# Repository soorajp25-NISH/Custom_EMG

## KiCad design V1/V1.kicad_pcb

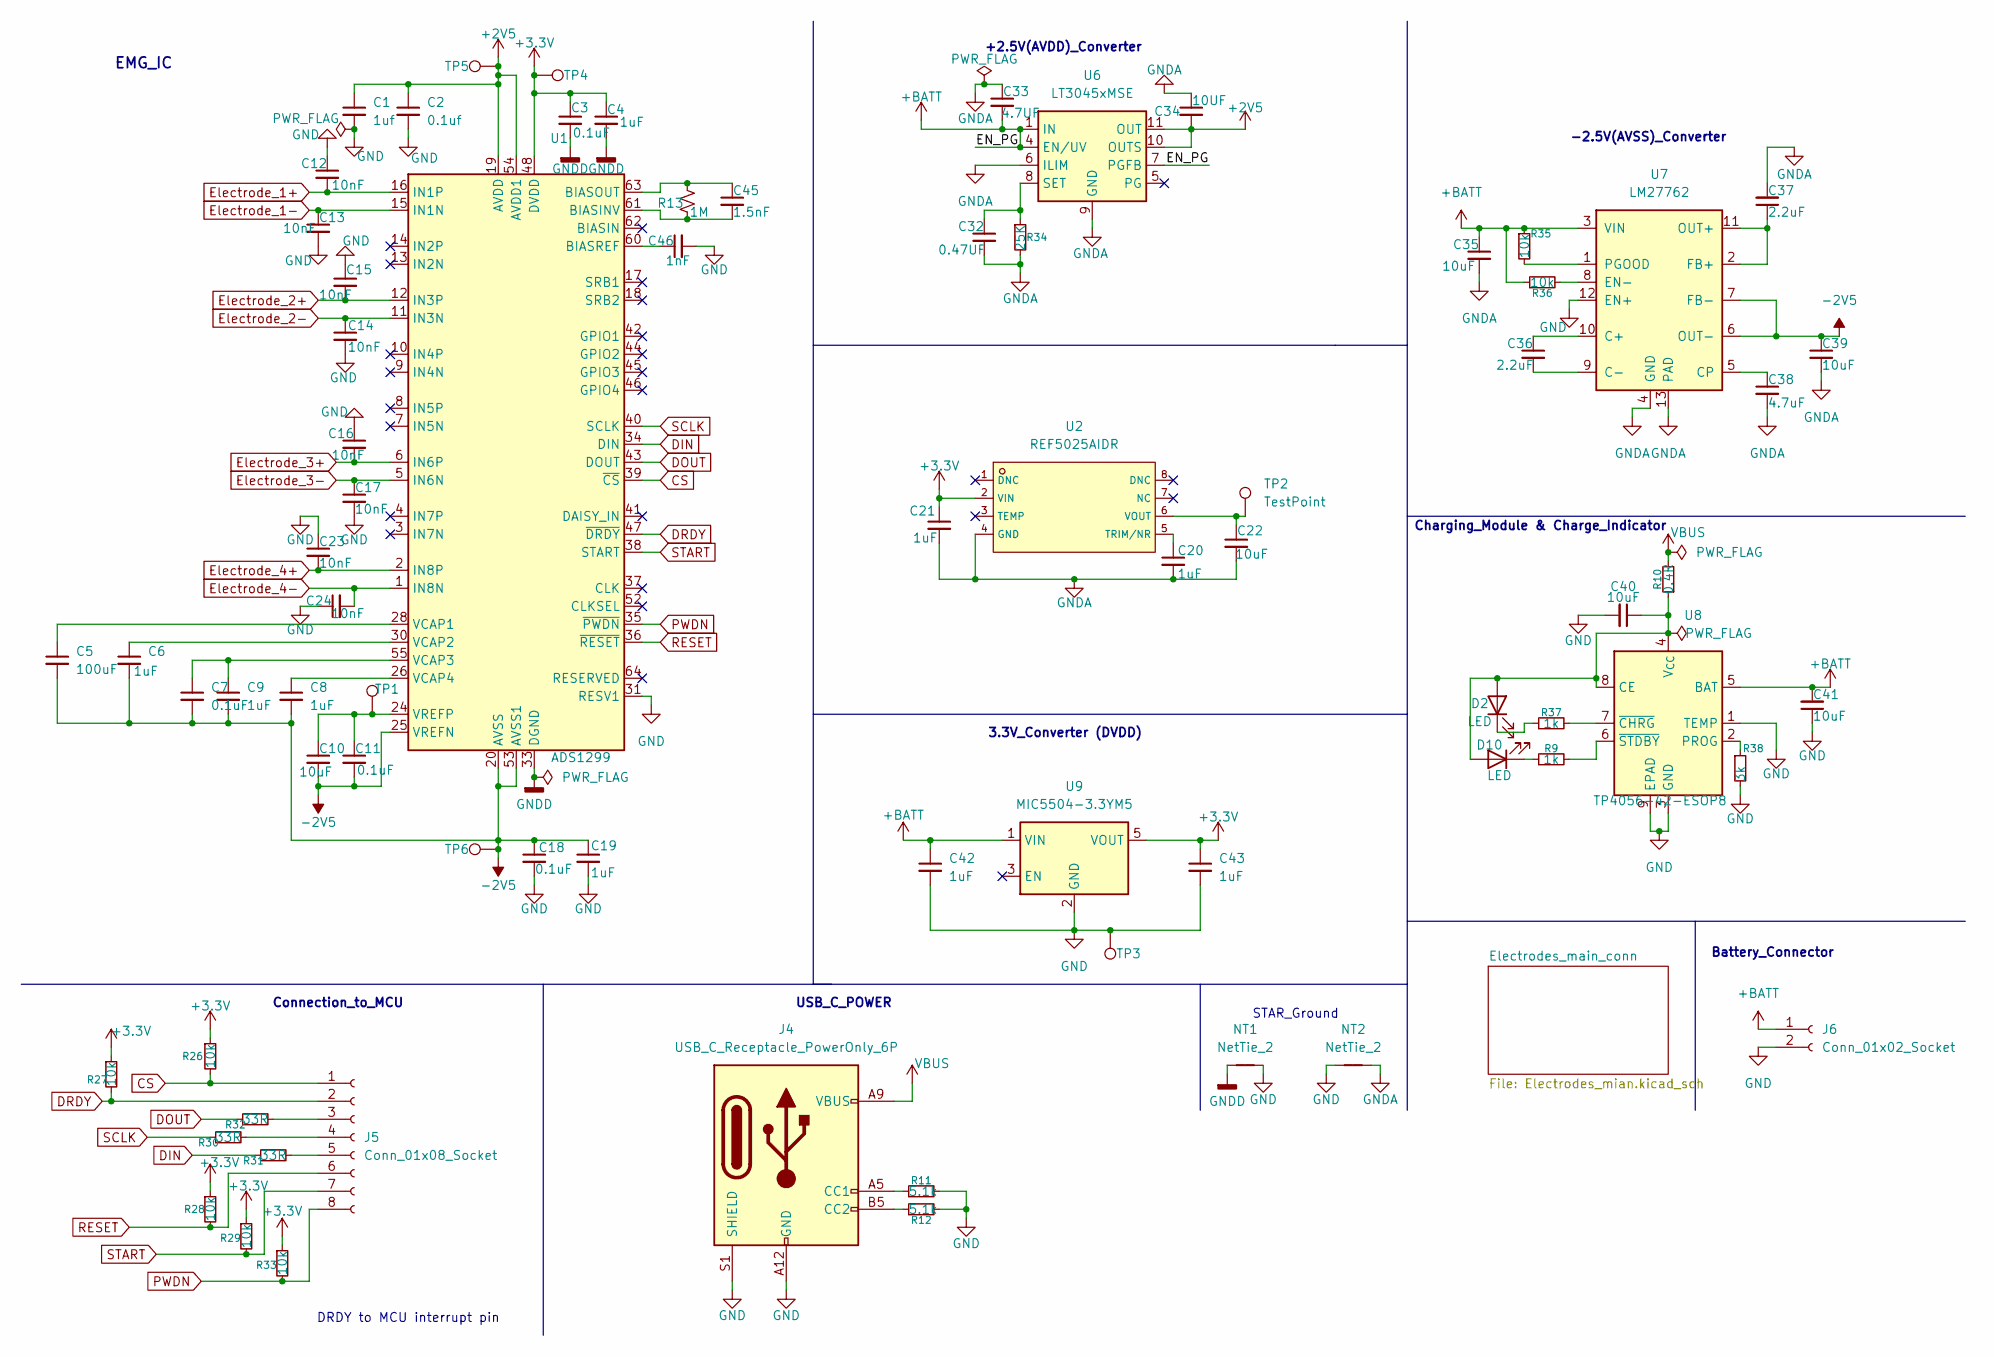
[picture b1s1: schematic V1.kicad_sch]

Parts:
C1: 1uf; C_0402_1005Metric
C2: 0.1uf; C_0402_1005Metric
C3, C7, C11, C18: 0.1uF; C_0402_1005Metric
C4, C6, C8, C9, C19: 1uF; C_0402_1005Metric
C5: 100uF; C_0603_1608Metric
C10, C35, C40, C41: 10uF; C_0603_1608Metric
C12, C13, C14, C15, C16, C17, C23, C24: 10nF; C_0402_1005Metric
C20, C21: 1uF; C_0603_1608Metric_Pad1.08x0.95mm_HandSolder
C22, C39: 10uF; C_0603_1608Metric_Pad1.08x0.95mm_HandSolder
C32: 0.47UF; C_0402_1005Metric
C33: 4.7UF; C_0603_1608Metric
C34: 10UF; C_0603_1608Metric
C36, C37: 2.2uF; C_0603_1608Metric
C38: 4.7uF; C_0603_1608Metric
C42, C43: 1uF; C_0603_1608Metric
C45: 1.5nF; C_0402_1005Metric
C46: 1nF; C_0402_1005Metric
D2, D10: LED; LED_0603_1608Metric_Pad1.05x0.95mm_HandSolder
J4: USB_C_Receptacle_PowerOnly_6P; USB_C_Receptacle_GCT_USB4135-GF-A_6P_TopMnt_Horizontal
J5: Conn_01x08_Socket; PinHeader_1x08_P2.54mm_Vertical_SMD_Pin1Right
J6: Conn_01x02_Socket; PinHeader_1x02_P2.54mm_Vertical
NT1, NT2: NetTie_2; NetTie-2_SMD_Pad0.5mm
R9, R37: 1k; R_0603_1608Metric_Pad0.98x0.95mm_HandSolder
R10: 0.4R; R_0603_1608Metric_Pad0.98x0.95mm_HandSolder
R11, R12: 5.1k; R_0603_1608Metric_Pad0.98x0.95mm_HandSolder
R13: 1M; R_0805_2012Metric
R26, R27, R28, R29, R33, R35, R36: 10k; R_0603_1608Metric_Pad0.98x0.95mm_HandSolder
R30, R31, R32: 33R; R_0603_1608Metric_Pad0.98x0.95mm_HandSolder
R34: 25K; R_0201_0603Metric_Pad0.64x0.40mm_HandSolder
R38: 3k; R_0603_1608Metric_Pad0.98x0.95mm_HandSolder
TP1, TP2, TP3, TP4, TP5, TP6: TestPoint; TestPoint_Pad_1.0x1.0mm
U1: ADS1299; TQFP-64_10x10mm_P0.5mm
U2: REF5025AIDR; SOIC-8_L4.9-W3.9-P1.27-LS6.0-BL; LCSC C11341
U6: LT3045xMSE; MSOP-12-1EP_3x4.039mm_P0.65mm_EP1.651x2.845mm
U7: LM27762; WSON-12-1EP_3x2mm_P0.5mm_EP1x2.65_ThermalVias
U8: TP4056-42-ESOP8; SOIC-8-1EP_3.9x4.9mm_P1.27mm_EP2.41x3.3mm_ThermalVias
U9: MIC5504-3.3YM5; SOT-23-5

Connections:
+2V5: C1.1, C2.1, C34.2, TP5.1, U1.19 (AVDD), U1.21 (AVDD), U1.22 (AVDD), U1.54 (AVDD1), U1.56 (AVDD), U1.59 (AVDD), U6.10 (OUTS), U6.11 (OUT), U6.12 (OUT)
+3.3V: C3.1, C4.1, C21.1, C43.1, R26.1, R27.1, R28.1, R29.1, R33.1, TP4.1, U1.48 (DVDD), U1.50 (DVDD), U2.2 (VIN), U9.5 (VOUT)
+BATT: C33.2, C35.1, C41.2, C42.1, J6.1, R35.1, R36.1, U6.1 (IN), U6.2 (IN), U6.3 (IN), U6.4 (EN/UV), U6.7 (PGFB), U7.3 (VIN), U8.5 (BAT), U9.1 (VIN)
-2V5: C5.2, C6.2, C7.2, C8.2, C9.2, C10.2, C11.2, C18.1, C19.1, C39.1, TP6.1, U1.20 (AVSS), U1.23 (AVSS), U1.25 (VREFN), U1.32 (AVSS), U1.53 (AVSS1), U1.57 (AVSS), U1.58 (AVSS), U7.6 (OUT-), U7.7 (FB-)
CS: J5.1, R26.2, U1.39 (~CS)
DIN: R31.1, U1.34 (DIN)
DOUT: R32.1, U1.43 (DOUT)
DRDY: J5.2, R27.2, U1.47 (~DRDY)
Electrode_1+: C12.2, U1.16 (IN1P); also elsewhere on the board
Electrode_1-: C13.1, U1.15 (IN1N); also elsewhere on the board
Electrode_2+: C15.2, U1.12 (IN3P); also elsewhere on the board
Electrode_2-: C14.1, U1.11 (IN3N); also elsewhere on the board
Electrode_3+: C16.2, U1.6 (IN6P); also elsewhere on the board
Electrode_3-: C17.1, U1.5 (IN6N); also elsewhere on the board
Electrode_4+: C23.2, U1.2 (IN8P); also elsewhere on the board
Electrode_4-: C24.2, U1.1 (IN8N); also elsewhere on the board
GND: C1.2, C2.2, C12.1, C13.2, C14.2, C15.1, C16.1, C17.2, C18.2, C19.2, C23.1, C24.1, C40.2, C41.1, C42.2, C43.2, C46.2, J4.A12 (GND), J4.B12 (GND), J4.S1 (SHIELD), J6.2, NT1.2, NT2.1, R11.2, R12.2, R38.2, TP3.1, U1.31 (RESV1), U7.12 (EN+), U8.1 (TEMP), U8.3 (GND), U8.9 (EPAD), U9.2 (GND); also elsewhere on the board
GNDA: C20.2, C21.2, C22.2, C32.2, C33.1, C34.1, C35.2, C37.2, C38.2, C39.2, NT2.2, R34.2, U2.4 (GND), U6.6 (ILIM), U6.9 (GND), U6.13 (GND), U7.4 (GND), U7.13 (PAD)
GNDD: C3.2, C4.2, NT1.1, U1.33 (DGND), U1.49 (DGND), U1.51 (DGND)
unnamed: D2.1 (K), R37.1
unnamed: C40.1, D2.2 (A), D10.2 (A), R10.1, U8.4 (V_{CC}), U8.8 (CE)
unnamed: D10.1 (K), R9.1
unnamed: J4.A5 (CC1), R11.1
unnamed: J4.B5 (CC2), R12.1
unnamed: J5.3, R32.2
unnamed: J5.4, R30.2
unnamed: J5.5, R31.2
unnamed: C45.2, R13.2, U1.61 (BIASINV)
unnamed: C45.1, R13.1, U1.63 (BIASOUT)
unnamed: C46.1, U1.60 (BIASREF)
unnamed: C5.1, U1.28 (VCAP1)
unnamed: C6.1, U1.30 (VCAP2)
unnamed: C7.1, C9.1, U1.55 (VCAP3)
unnamed: C8.1, U1.26 (VCAP4)
unnamed: C10.1, C11.1, TP1.1, U1.24 (VREFP)
unnamed: C20.1, U2.5 (TRIM/NR)
unnamed: C22.1, TP2.1, U2.6 (VOUT)
unnamed: C32.1, R34.1, U6.8 (SET)
unnamed: C36.1, U7.10 (C+)
unnamed: C36.2, U7.9 (C-)
unnamed: C38.1, U7.5 (CP)
unnamed: R36.2, U7.8 (EN-)
unnamed: C37.1, U7.2 (FB+), U7.11 (OUT+)
unnamed: R35.2, U7.1 (PGOOD)
unnamed: R38.1, U8.2 (PROG)
unnamed: R37.2, U8.7 (~CHRG)
unnamed: R9.2, U8.6 (~STDBY)
PWDN: J5.8, R33.2, U1.35 (~PWDN)
RESET: J5.6, R28.2, U1.36 (~RESET)
SCLK: R30.1, U1.40 (SCLK)
START: J5.7, R29.2, U1.38 (START)
VBUS: J4.A9 (VBUS), J4.B9 (VBUS), R10.2

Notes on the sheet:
Battery_Connector
Charging_Module & Charge_Indicator
-2.5V(AVSS)_Converter
3.3V_Converter (DVDD)
+2.5V(AVDD)_Converter
STAR_Ground
DRDY to MCU interrupt pin
Connection_to_MCU
USB_C_POWER
EMG_IC

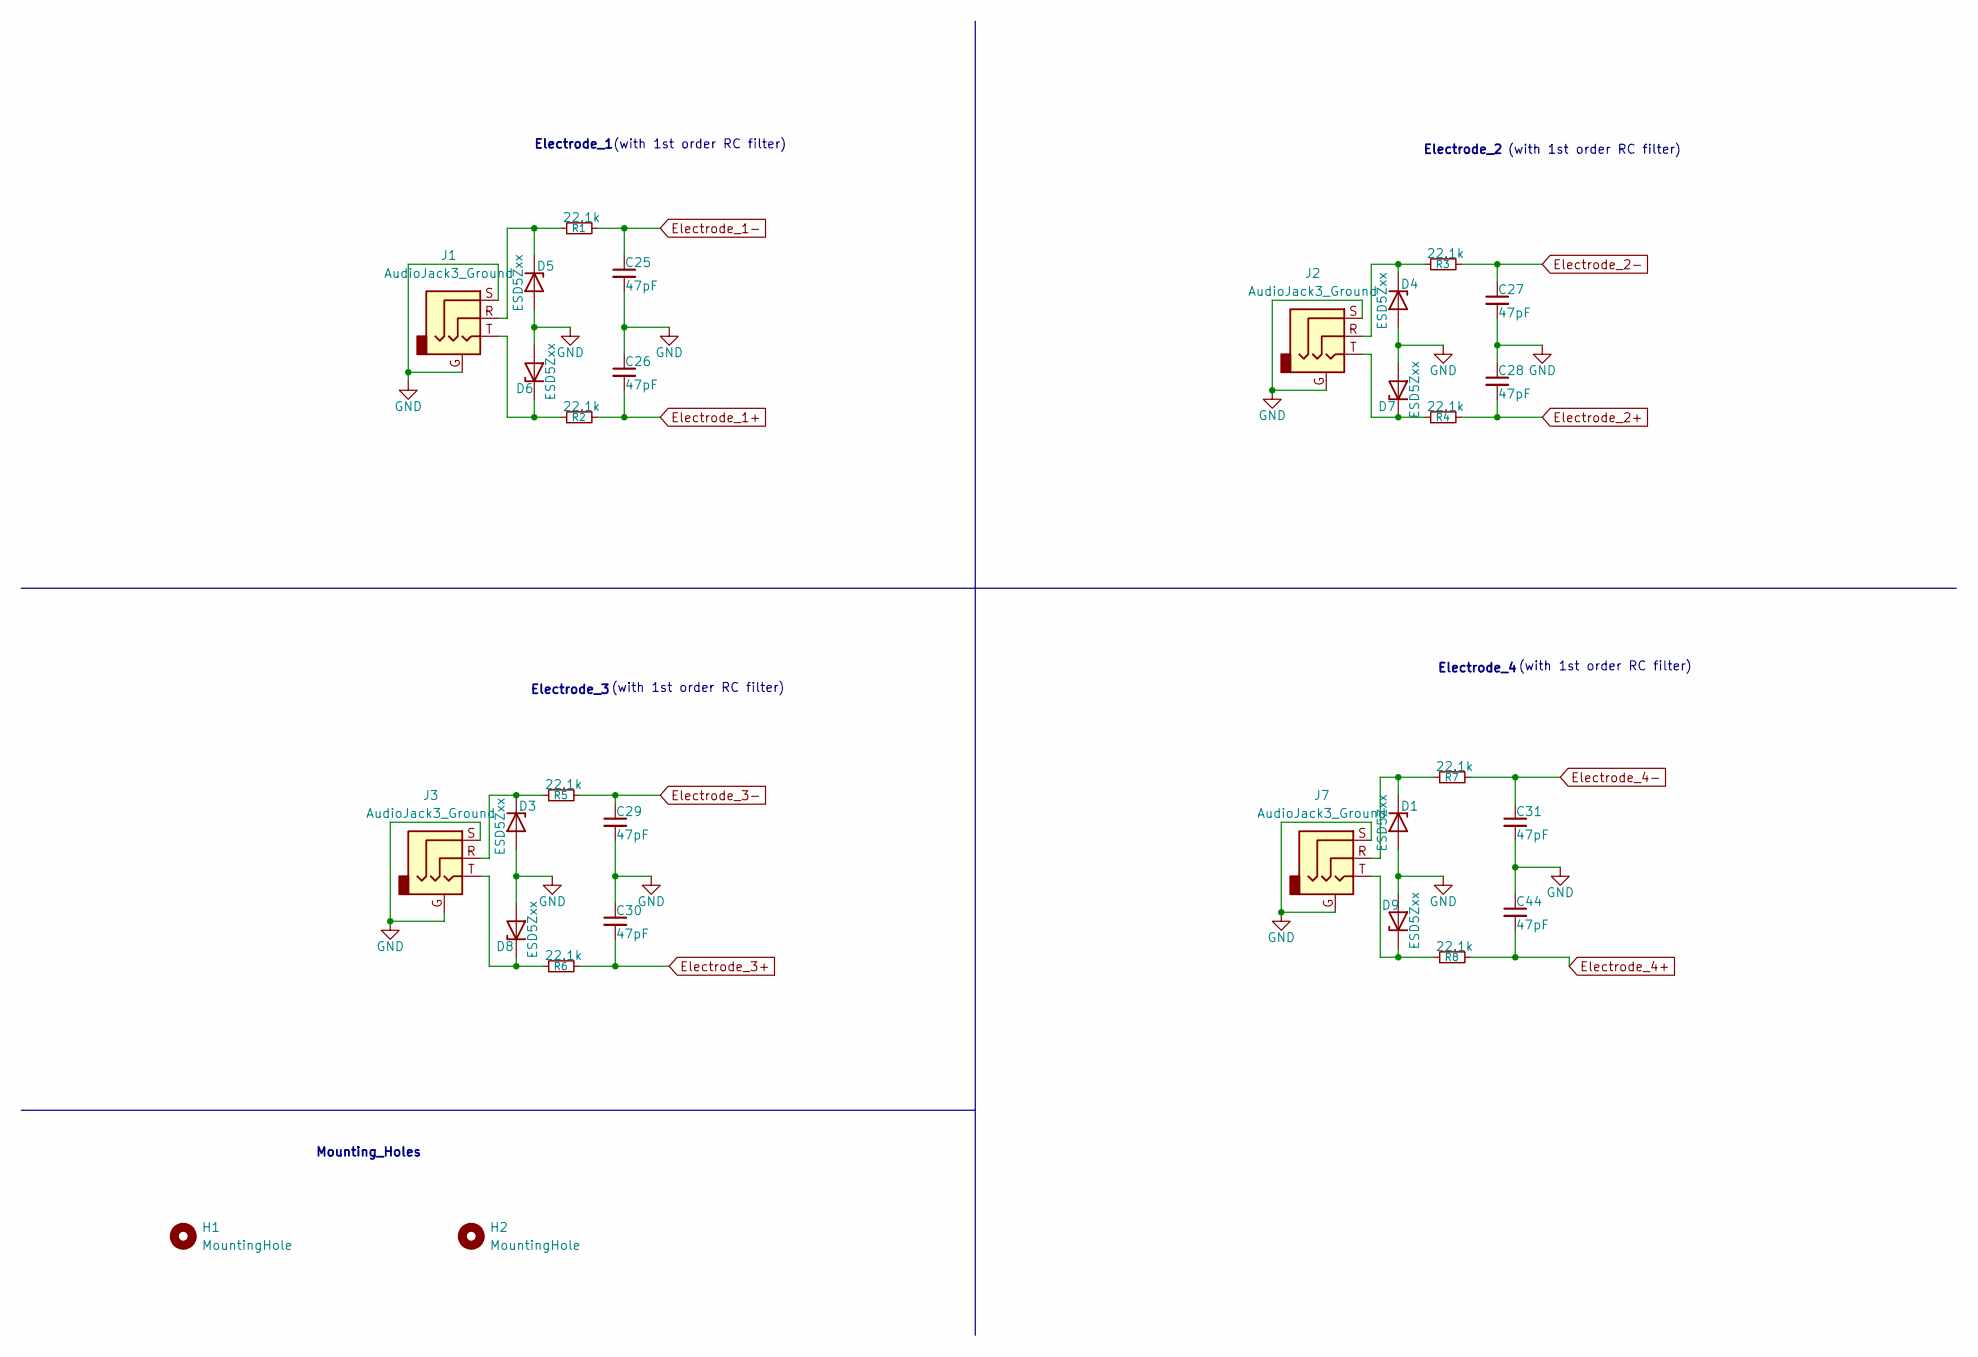
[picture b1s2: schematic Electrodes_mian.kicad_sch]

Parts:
C25, C26, C27, C28, C29, C30, C31, C44: 47pF; C_0603_1608Metric
D1, D3, D4, D5, D6, D7, D8, D9: ESD5Zxx; D_SOD-523
H1, H2: MountingHole; MountingHole_2.1mm
J1, J2, J3, J7: AudioJack3_Ground; Jack_3.5mm_CUI_SJ-3524-SMT_Horizontal
R1, R2, R3, R4, R5, R6, R7, R8: 22.1k; R_0603_1608Metric

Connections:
Electrode_1+: C26.2, R2.2; also elsewhere on the board
Electrode_1-: C25.1, R1.2; also elsewhere on the board
Electrode_2+: C28.2, R4.2; also elsewhere on the board
Electrode_2-: C27.1, R3.2; also elsewhere on the board
Electrode_3+: C30.2, R6.2; also elsewhere on the board
Electrode_3-: C29.1, R5.2; also elsewhere on the board
Electrode_4+: C44.2, R8.2; also elsewhere on the board
Electrode_4-: C31.1, R7.2; also elsewhere on the board
GND: C25.2, C26.1, C27.2, C28.1, C29.2, C30.1, C31.2, C44.1, D1.2 (A), D3.2 (A), D4.2 (A), D5.2 (A), D6.2 (A), D7.2 (A), D8.2 (A), D9.2 (A), J1.G, J1.S, J2.G, J2.S, J3.G, J3.S, J7.G, J7.S; also elsewhere on the board
unnamed: D1.1 (K), J7.R, R7.1
unnamed: D3.1 (K), J3.R, R5.1
unnamed: D4.1 (K), J2.R, R3.1
unnamed: D5.1 (K), J1.R, R1.1
unnamed: D6.1 (K), J1.T, R2.1
unnamed: D7.1 (K), J2.T, R4.1
unnamed: D8.1 (K), J3.T, R6.1
unnamed: D9.1 (K), J7.T, R8.1

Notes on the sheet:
Mounting_Holes
(with 1st order RC filter)
Electrode_2
Electrode_3
Electrode_4
Electrode_1

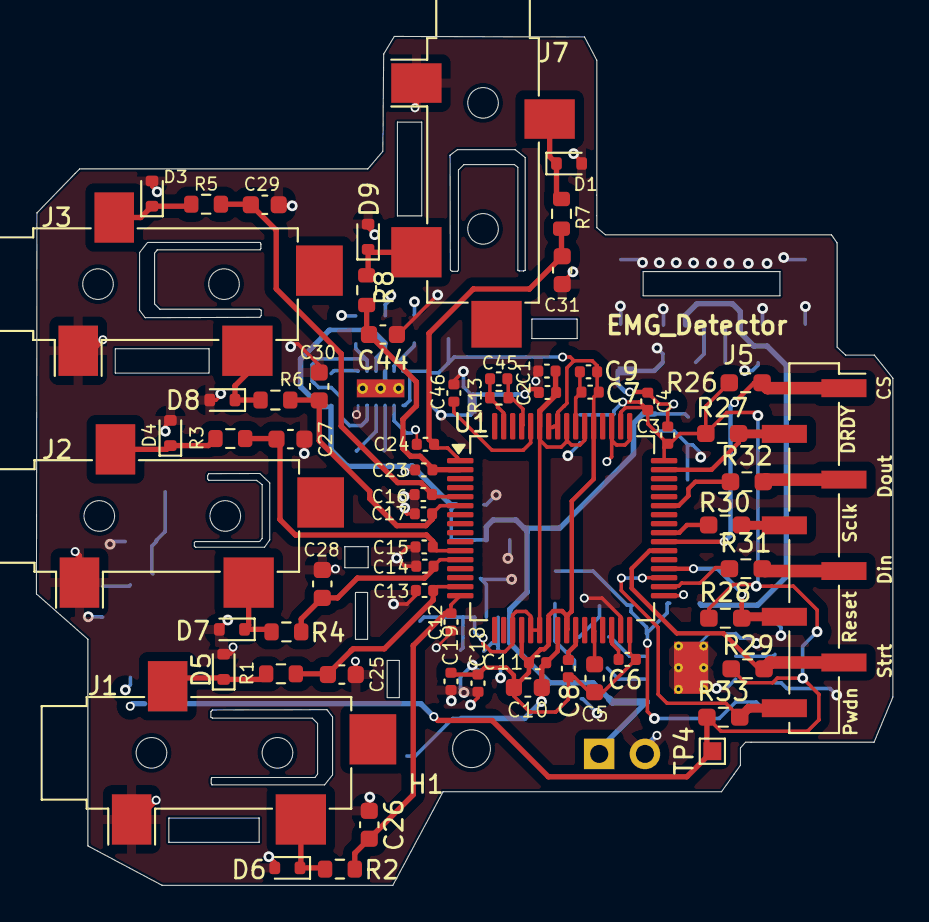
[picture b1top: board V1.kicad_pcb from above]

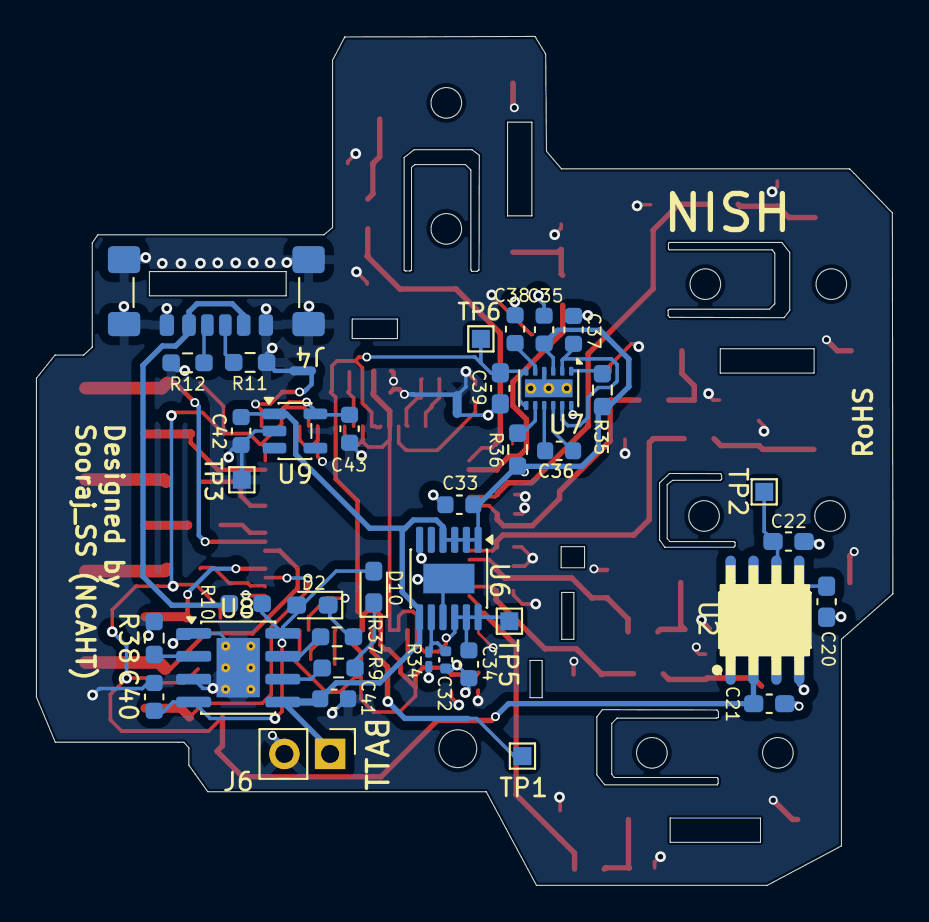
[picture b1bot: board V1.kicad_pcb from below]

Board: 4 copper layers, 47.6 x 47.2 mm, 105 parts (40 on the bottom side), 60 nets.

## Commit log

2026-03-06 Primary EMG signal detection PCB Layout completed
2026-05-22 pcb design updated
2026-05-26 design updated
2026-05-26 all tracks routing done
2026-06-02 pcb design updated based on the suggestions.
